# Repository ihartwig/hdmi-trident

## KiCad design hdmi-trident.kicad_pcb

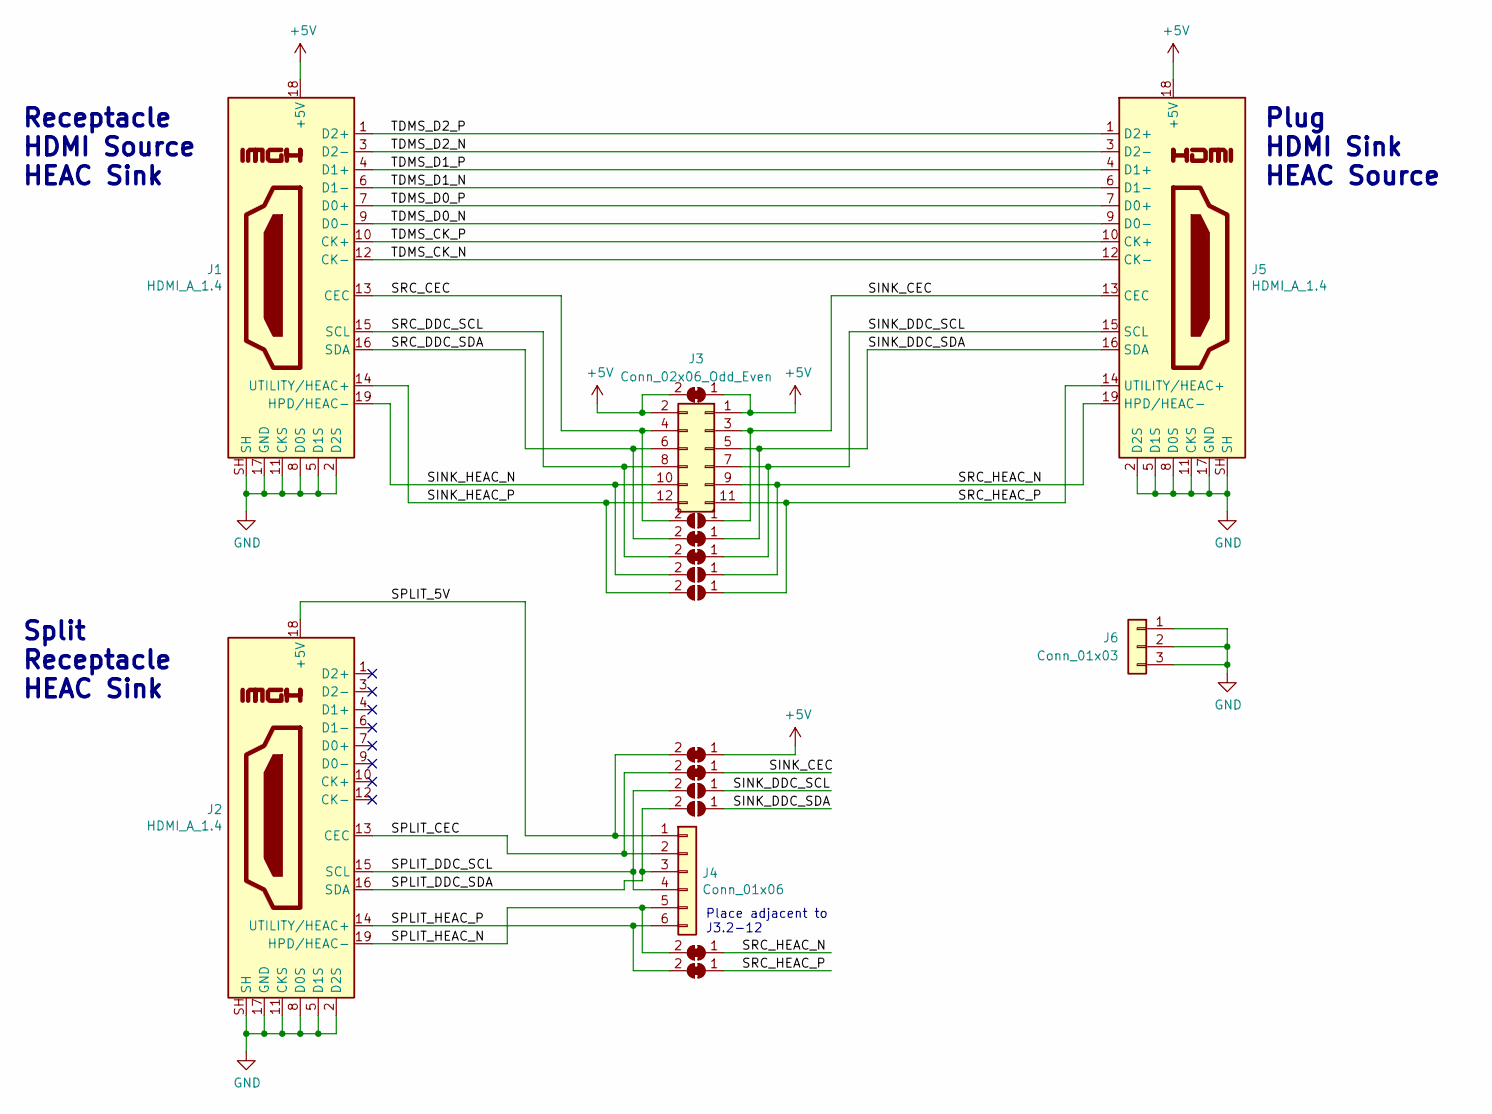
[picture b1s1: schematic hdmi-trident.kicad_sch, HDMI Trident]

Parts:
J1, J2: HDMI_A_1.4; HDMI_A_Rcpt_Vert_3Post
J3: Conn_02x06_Odd_Even; PinHeader_2x06_P2.54mm_Vertical
J4: Conn_01x06; PinHeader_1x06_P2.54mm_Vertical
J5: HDMI_A_1.4; HDMI_A_Plug_Horizontal_EdgeMount
J6: Conn_01x03; PinSocket_1x03_P2.54mm_Vertical
JP1, JP3, JP4, JP7, JP8, JP11, JP12: SolderJumper_2_Bridged; SolderJumper-2_P1.3mm_Bridged_RoundedPad1.0x1.5mm
JP2, JP5, JP6, JP9, JP10: SolderJumper_2_Open; SolderJumper-2_P1.3mm_Open_RoundedPad1.0x1.5mm

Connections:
+5V: J1.18 (+5V), J3.1, J3.2, J5.18 (+5V), JP1.1 (A), JP1.2 (B), JP7.1 (A)
/SINK_CEC: J3.3, J5.13 (CEC), JP2.1 (A), JP8.1 (A)
/SINK_DDC_SCL: J3.7, J5.15 (SCL), JP4.1 (A), JP9.1 (A)
/SINK_DDC_SDA: J3.5, J5.16 (SDA), JP3.1 (A), JP10.1 (A)
/SINK_HEAC_N: J1.19 (HPD/HEAC-), J3.10, JP5.2 (B)
/SINK_HEAC_P: J1.14 (UTILITY/HEAC+), J3.12, JP6.2 (B)
/SPLIT_5V: J2.18 (+5V), J4.1, JP7.2 (B)
/SPLIT_CEC: J2.13 (CEC), J4.2, JP8.2 (B)
/SPLIT_DDC_SCL: J2.15 (SCL), J4.4, JP9.2 (B)
/SPLIT_DDC_SDA: J2.16 (SDA), J4.3, JP10.2 (B)
/SPLIT_HEAC_N: J2.19 (HPD/HEAC-), J4.5, JP11.2 (B)
/SPLIT_HEAC_P: J2.14 (UTILITY/HEAC+), J4.6, JP12.2 (B)
/SRC_CEC: J1.13 (CEC), J3.4, JP2.2 (B)
/SRC_DDC_SCL: J1.15 (SCL), J3.8, JP4.2 (B)
/SRC_DDC_SDA: J1.16 (SDA), J3.6, JP3.2 (B)
/SRC_HEAC_N: J3.9, J5.19 (HPD/HEAC-), JP5.1 (A), JP11.1 (A)
/SRC_HEAC_P: J3.11, J5.14 (UTILITY/HEAC+), JP6.1 (A), JP12.1 (A)
/TDMS_CK_N: J1.12 (CK-), J5.12 (CK-)
/TDMS_CK_P: J1.10 (CK+), J5.10 (CK+)
/TDMS_D0_N: J1.9 (D0-), J5.9 (D0-)
/TDMS_D0_P: J1.7 (D0+), J5.7 (D0+)
/TDMS_D1_N: J1.6 (D1-), J5.6 (D1-)
/TDMS_D1_P: J1.4 (D1+), J5.4 (D1+)
/TDMS_D2_N: J1.3 (D2-), J5.3 (D2-)
/TDMS_D2_P: J1.1 (D2+), J5.1 (D2+)
GND: J1.2 (D2S), J1.5 (D1S), J1.8 (D0S), J1.11 (CKS), J1.17 (GND), J1.SH, J2.2 (D2S), J2.5 (D1S), J2.8 (D0S), J2.11 (CKS), J2.17 (GND), J2.SH, J5.2 (D2S), J5.5 (D1S), J5.8 (D0S), J5.11 (CKS), J5.17 (GND), J5.SH, J6.1, J6.2, J6.3

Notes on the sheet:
Place adjacent to J3.2-12
Receptacle HDMI Source HEAC Sink
Plug HDMI Sink HEAC Source
Split Receptacle HEAC Sink

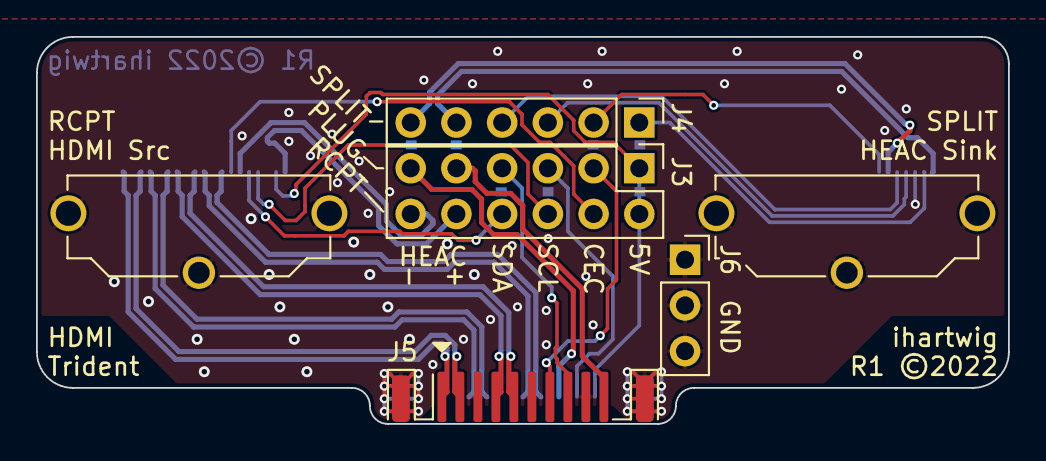
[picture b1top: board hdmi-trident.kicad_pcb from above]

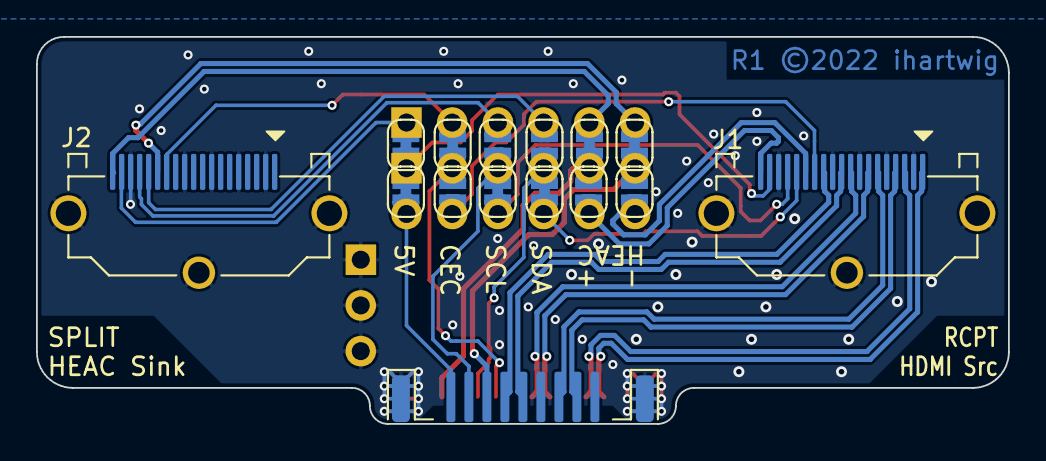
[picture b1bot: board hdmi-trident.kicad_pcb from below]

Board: 2 copper layers, 54.0 x 21.5 mm, 18 parts (14 on the bottom side), 26 nets.

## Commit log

2022-02-22 initial project, schematic, layout
2022-10-30 change rcpt to vertical smt w/ new board shape
2022-10-30 cleanup graphics and add new R1 gerbers

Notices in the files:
hdmi-trident.kicad_pcb:
R1 ©2022 ihartwig
R1 ©2022
